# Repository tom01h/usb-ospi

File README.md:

# PCとFPGAをUSB接続する

## 概要
以下の接続でPCとFPGA間の高速転送をしたいプロジェクト。  
今はRead120Mbps,Write100Mbpsくらい。  
LinuxPC ←(USB-HS)→ USB3300 ←(ULPI)→ STM32H7B0 ←(OCTO SPI)→ FPGA

FPGA内ではAXIマスターポートをつける予定だけど、まだSPIクロックで動くBRAMにアクセスできるだけ。

USB転送はPCでは[libusb](https://github.com/libusb/libusb)、STM32では[tinyusb](https://github.com/hathach/tinyusb)を使ってVendorSpecificなバルク転送をします。  
OCTO SPIはSTM32はHALを使って、FPGAは適当に作ったRTLを使います。

## 部品
- PCはLinuxPCならたぶん何でもよい
- 基板を1枚こしらえました（[スケマ](https://github.com/tom01h/usb-ospi/blob/master/PCB/QMTECH/ospi.pdf)）
    - この基板の動作確認は200Tのみ
    - [8ピンのデータ用type-Cコネクタ](https://ja.aliexpress.com/item/1005004277420642.html)
    - [6ピンの電源用type-Cコネクタ](https://ja.aliexpress.com/item/1005004384274891.html)
    - USB3300-EZK
    - 24MHz 3225 のパッシブクォーツ水晶発振器 (2と4がグランド)
    - 1206 の抵抗とかコンデンサ
    - コネクタは次の組み合わせでぎりぎり干渉しない
        - STM32をとめる[コネクタ](https://ja.aliexpress.com/item/32892386779.html)
        - FPGAをとめる[コネクタオス](https://ja.aliexpress.com/item/1005004843759392.html)
            - これの11.2を、ピンが基板からはみ出ないところまでプラスチックをずらして使用
            - メスは普通のやつ
    - 他…
- QMTECHのFPGA (どっちか1個)
    - [200T](https://ja.aliexpress.com/item/1005002960622091.html)
    - [100T](https://ja.aliexpress.com/item/4000170003461.html)
- STM32H7
    - [WeActStudioのボード](https://ja.aliexpress.com/item/1005004466900940.html)
## 使い方
### ホスト
```
cd host/
cmake .
make
sudo ./main
```
### ファームウェア
- `firm/tinyusb`の下にtinyusbをクローンする
    - このリポジトリにあるファイルで上書きする
- usb_octospi.iocからプロジェクトを作る
    - このリポジトリにあるファイルで上書きする
- [ここ](https://github.com/hathach/tinyusb/discussions/633)に従って参照パスを追加する
```
- Right click the project, go to properties. in C/C++ General -> Paths and Symbols, in the "Includes" tab add a path, make it a workspace path, point it to the tinyusb/src directory. Then, in the "Source Location" tab, add folder, and also point it to tinyusb/src
- Add a tusb_config.h to your "Core/Inc"
```
### FPGA
- [なひビバ](https://github.com/tokuden/NahiViva)で次のどちらかのプロジェクトを再生してビルドする
    - QMT100/
    - QMT200/

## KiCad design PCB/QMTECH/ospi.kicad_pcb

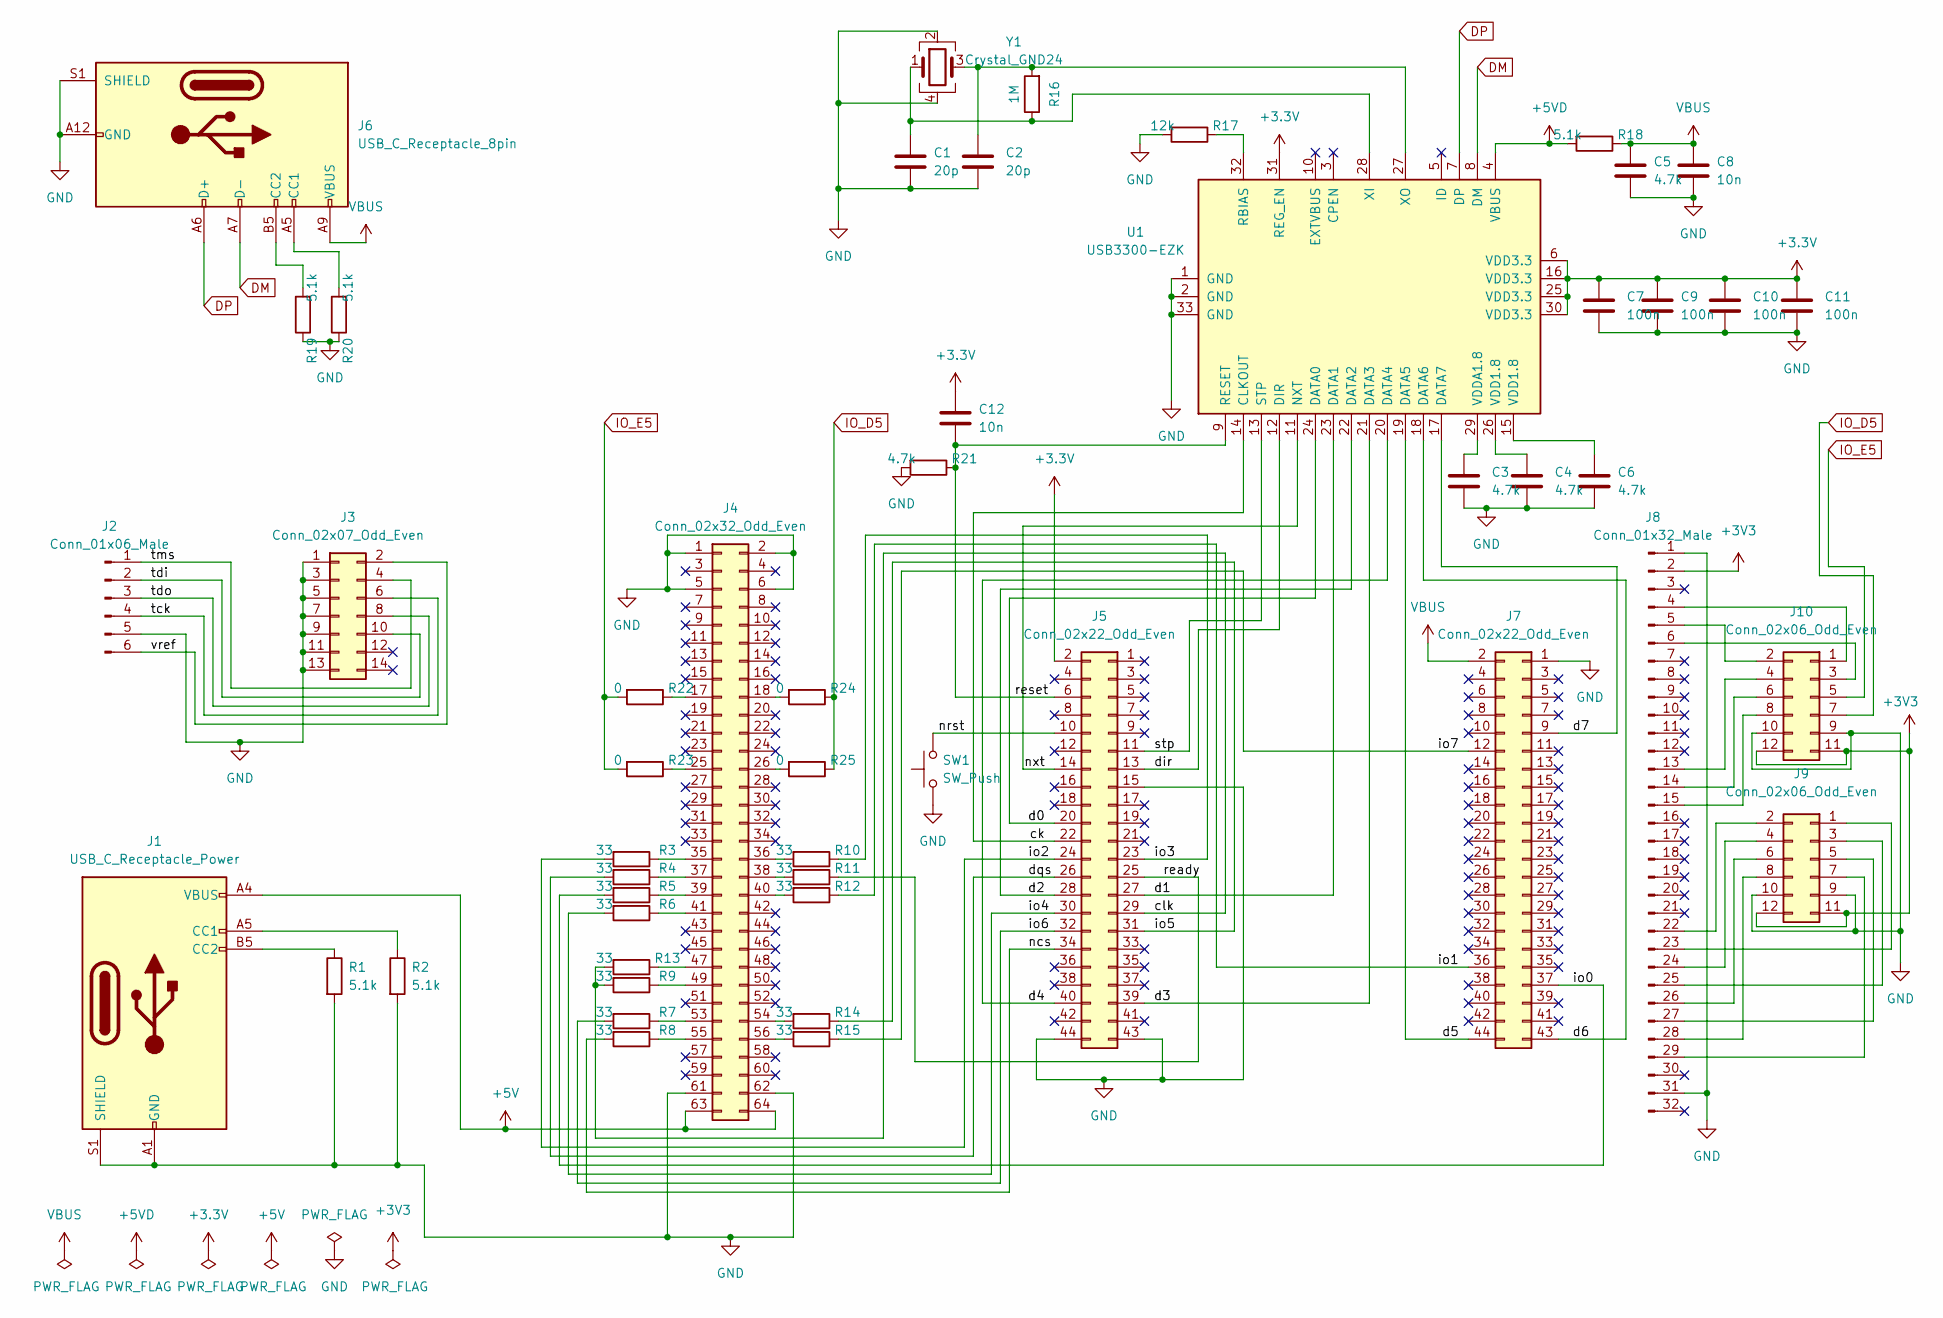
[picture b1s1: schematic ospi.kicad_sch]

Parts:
C1, C2: 20p; C_1206_3216Metric_Pad1.33x1.80mm_HandSolder
C3, C4, C5, C6: 4.7k; C_1206_3216Metric_Pad1.33x1.80mm_HandSolder
C7, C9, C10, C11: 100n; C_1206_3216Metric_Pad1.33x1.80mm_HandSolder
C8, C12: 10n; C_1206_3216Metric_Pad1.33x1.80mm_HandSolder
J1: USB_C_Receptacle_Power
J2: Conn_01x06_Male; PinSocket_1x06_P2.54mm_Vertical
J3: Conn_02x07_Odd_Even; PinHeader_2x07_P2.00mm_Vertical
J4: Conn_02x32_Odd_Even; PinSocket_2x32_P2.54mm_Vertical
J5, J7: Conn_02x22_Odd_Even; PinSocket_2x22_P2.54mm_Vertical
J6: USB_C_Receptacle_8pin
J8: Conn_01x32_Male; PinSocket_1x32_P2.54mm_Vertical
J9, J10: Conn_02x06_Odd_Even; PinSocket_2x06_P2.54mm_Vertical
R1, R2, R18, R19, R20: 5.1k; R_1206_3216Metric_Pad1.30x1.75mm_HandSolder
R3, R4, R5, R6, R7, R8, R9, R10, R11, R12, R13, R14, R15: 33; R_1206_3216Metric_Pad1.30x1.75mm_HandSolder
R16: 1M; R_1206_3216Metric_Pad1.30x1.75mm_HandSolder
R17: 12k; R_1206_3216Metric_Pad1.30x1.75mm_HandSolder
R21: 4.7k; R_1206_3216Metric_Pad1.30x1.75mm_HandSolder
R22, R23, R24, R25: 0; R_1206_3216Metric_Pad1.30x1.75mm_HandSolder
SW1: SW_Push; SW_SPST_CK_RS282G05A3
U1: USB3300-EZK; QFN-32-1EP_5x5mm_P0.5mm_EP3.45x3.45mm_ThermalVias
Y1: Crystal_GND24; Crystal_SMD_3225-4Pin_3.2x2.5mm_HandSoldering

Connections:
+3.3V: C7.1, C9.1, C10.1, C11.1, C12.1, J5.2, U1.6 (VDD3.3), U1.16 (VDD3.3), U1.25 (VDD3.3), U1.30 (VDD3.3), U1.31 (REG_EN)
+3V3: J8.2, J9.11, J9.12, J10.11, J10.12
+5V: J1.A4 (VBUS), J1.A9 (VBUS), J1.B4 (VBUS), J1.B9 (VBUS), J4.63, J4.64
+5VD: R18.2, U1.4 (VBUS)
/ck: J5.22, U1.14 (CLKOUT)
/clk: J5.29, R9.2, R13.2
/d0: J5.20, U1.24 (DATA0)
/d1: J5.27, U1.23 (DATA1)
/d2: J5.28, U1.22 (DATA2)
/d3: J5.39, U1.21 (DATA3)
/d4: J5.40, U1.20 (DATA4)
/d5: J7.44, U1.19 (DATA5)
/d6: J7.43, U1.18 (DATA6)
/d7: J7.9, U1.17 (DATA7)
/dir: J5.13, U1.12 (DIR)
/dqs: J5.26, R4.2
/io0: J7.37, R5.2
/io1: J7.36, R12.1
/io2: J5.24, R3.2
/io3: J5.23, R10.1
/io4: J5.30, R6.2
/io5: J5.31, R14.1
/io6: J5.32, R7.2
/io7: J7.12, R15.1
/ncs: J5.34, R8.2
/nrst: J5.10, SW1.2
/nxt: J5.14, U1.11 (NXT)
/ready: J5.25, R11.1
/reset: C12.2, J5.6, R21.1, U1.9 (RESET)
/stp: J5.11, U1.13 (STP)
/tck: J2.4, J3.6
/tdi: J2.2, J3.10
/tdo: J2.3, J3.8
/tms: J2.1, J3.4
/vref: J2.6, J3.2
DM: J6.A7 (D-), U1.8 (DM)
DP: J6.A6 (D+), U1.7 (DP)
GND: C1.2, C2.2, C3.2, C4.2, C5.2, C6.2, C7.2, C8.2, C9.2, C10.2, C11.2, J1.A1 (GND), J1.A12 (GND), J1.B1 (GND), J1.B12 (GND), J1.S1 (SHIELD), J2.5, J3.1, J3.3, J3.5, J3.7, J3.9, J3.11, J3.13, J4.1, J4.2, J4.5, J4.6, J4.61, J4.62, J5.15, J5.43, J5.44, J6.A12 (GND), J6.B12 (GND), J6.S1 (SHIELD), J7.1, J8.1, J8.31, J9.9, J9.10, J10.9, J10.10, R1.2, R2.2, R17.2, R19.1, R20.1, R21.2, SW1.1, U1.1 (GND), U1.2 (GND), U1.33 (GND), Y1.2, Y1.4
IO_D5: J10.7, R24.1, R25.1
IO_E5: J10.5, R22.2, R23.2
unnamed: C1.1, R16.1, U1.28 (XI), Y1.1
unnamed: C2.1, R16.2, U1.27 (XO), Y1.3
unnamed: C3.1, U1.29 (VDDA1.8)
unnamed: C4.1, U1.26 (VDD1.8)
unnamed: C6.1, U1.15 (VDD1.8)
unnamed: J1.A5 (CC1), R2.1
unnamed: J1.B5 (CC2), R1.1
unnamed: J4.17, R22.1
unnamed: J4.18, R24.2
unnamed: J4.25, R23.1
unnamed: J4.26, R25.2
unnamed: J4.35, R3.1
unnamed: J4.36, R10.2
unnamed: J4.37, R4.1
unnamed: J4.38, R11.2
unnamed: J4.39, R5.1
unnamed: J4.40, R12.2
unnamed: J4.41, R6.1
unnamed: J4.47, R13.1
unnamed: J4.49, R9.1
unnamed: J4.53, R7.1
unnamed: J4.54, R14.2
unnamed: J4.55, R8.1
unnamed: J4.56, R15.2
unnamed: J6.A5 (CC1), R20.2
unnamed: J6.B5 (CC2), R19.2
unnamed: J8.22, J9.2
unnamed: J8.23, J9.1
unnamed: J8.24, J9.4
unnamed: J8.25, J9.3
unnamed: J8.26, J9.6
unnamed: J8.27, J9.5
unnamed: J8.28, J9.8
unnamed: J8.29, J9.7
unnamed: J8.4, J10.1
unnamed: J8.5, J10.2
unnamed: J8.6, J10.3
unnamed: J8.13, J10.4
unnamed: J8.14, J10.6
unnamed: J8.15, J10.8
unnamed: R17.1, U1.32 (RBIAS)
VBUS: C5.1, C8.1, J6.A9 (VBUS), J6.B9 (VBUS), J7.2, R18.1

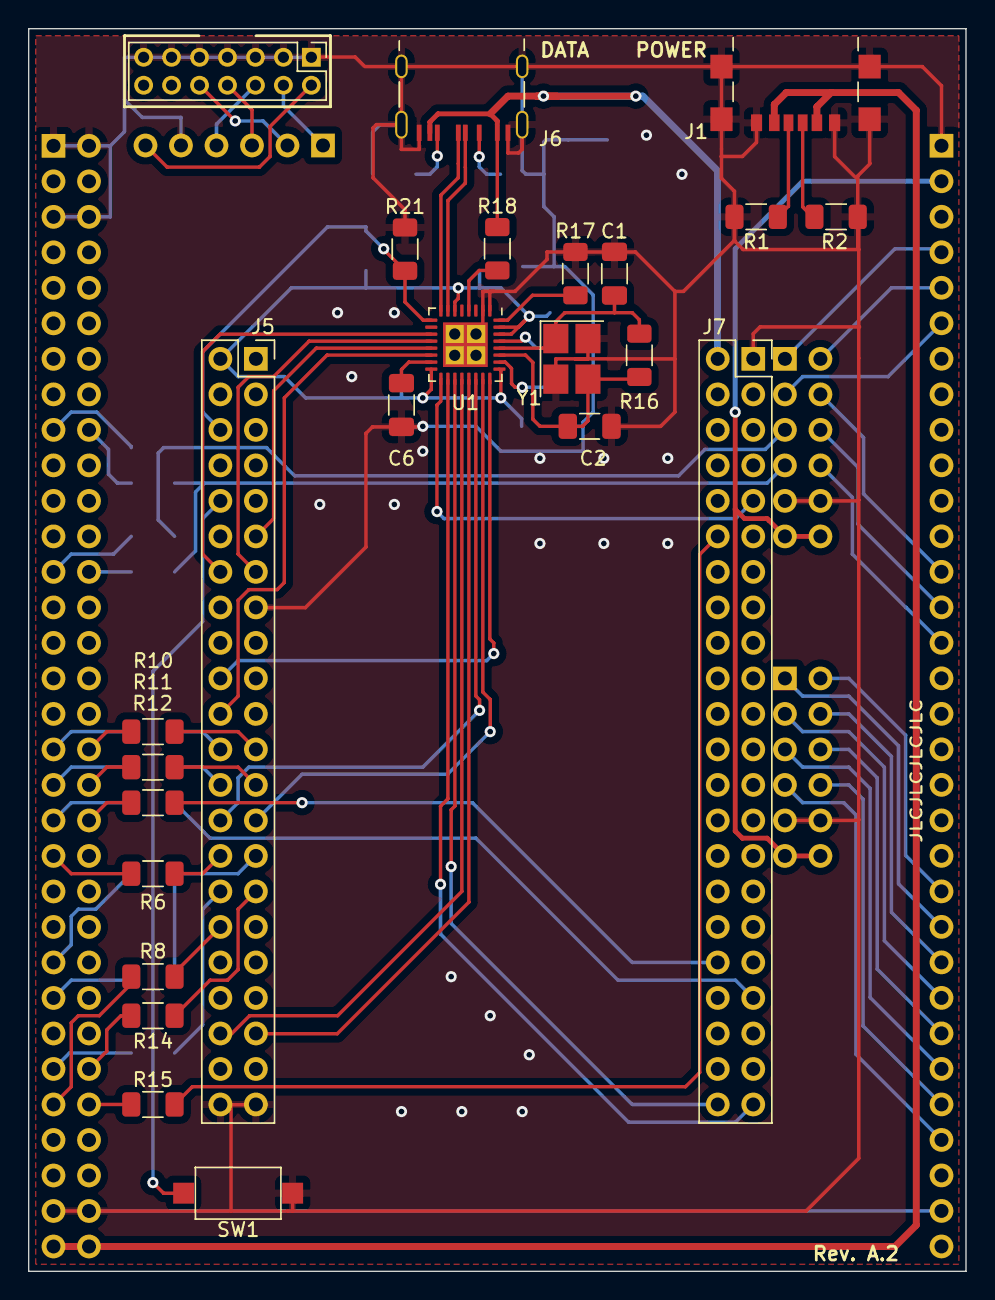
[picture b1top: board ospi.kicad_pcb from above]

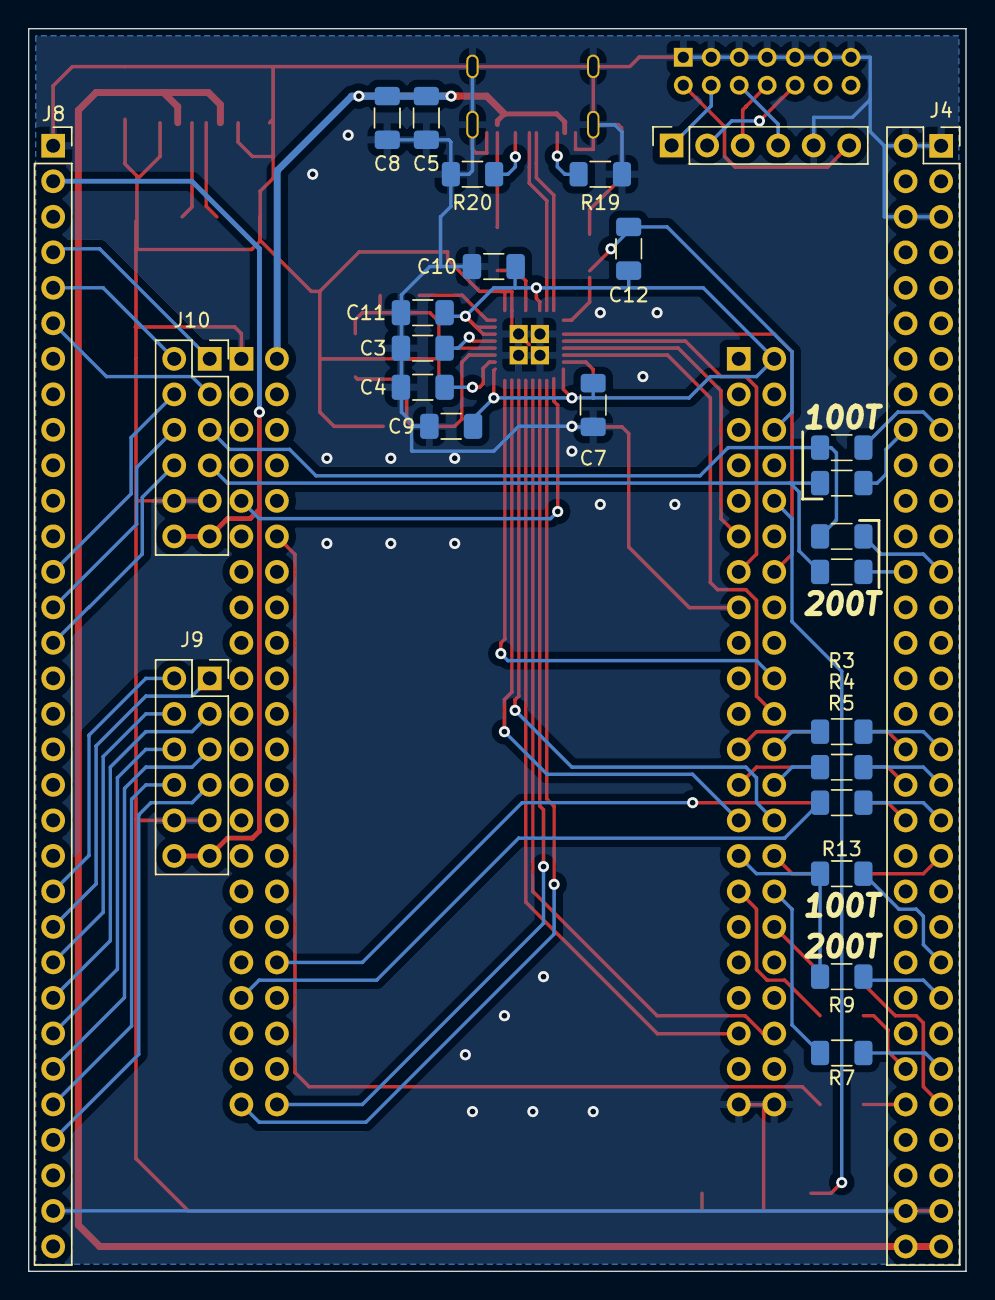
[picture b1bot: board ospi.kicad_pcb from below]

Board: 2 copper layers, 67.1 x 88.9 mm, 50 parts (26 on the bottom side), 82 nets.

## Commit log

2022-11-15 WRITE COMMAND
2022-11-19 READ COMMAND
2022-12-06 合成 QMT 100T
2022-12-06 ULPI
2022-12-22 tinyusb vendor class
2022-12-24 プロトコル WIP
    libusbの分割未対応
2022-12-26 プロトコル READのみ分割対応
    libusbは分割なし
    USBは512B
    OCTOSPIは256B (毎回新規コマンド)
2022-12-28 プロトコル分割 R/Wともに対応
2022-12-28 ダブルバッファ
2022-12-29 OCTO SPI 30->60MHz
2023-01-12 200T追加 クロックピン変更
2023-01-12 不要ファイル削除
2023-01-15 add PCB
2023-01-15 README WIP
2023-02-27 PCB更新
